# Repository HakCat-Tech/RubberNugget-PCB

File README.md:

# RubberNugget PCB v1.0 (alpha)
PCB design files for the RubberNugget.  More documentation coming soon!

## Features
- ESP32-S2 WiFi MicroController
- Native USB
- JTAG Debug
- Expansion Headers
- UART Breakout
- Qwiic Connector
- NeoPixel Breakout

## Fixes
- [ ] Antenna clearance
- [ ] Component layout
- [ ] Header pinout standard
- [ ] PCB Art

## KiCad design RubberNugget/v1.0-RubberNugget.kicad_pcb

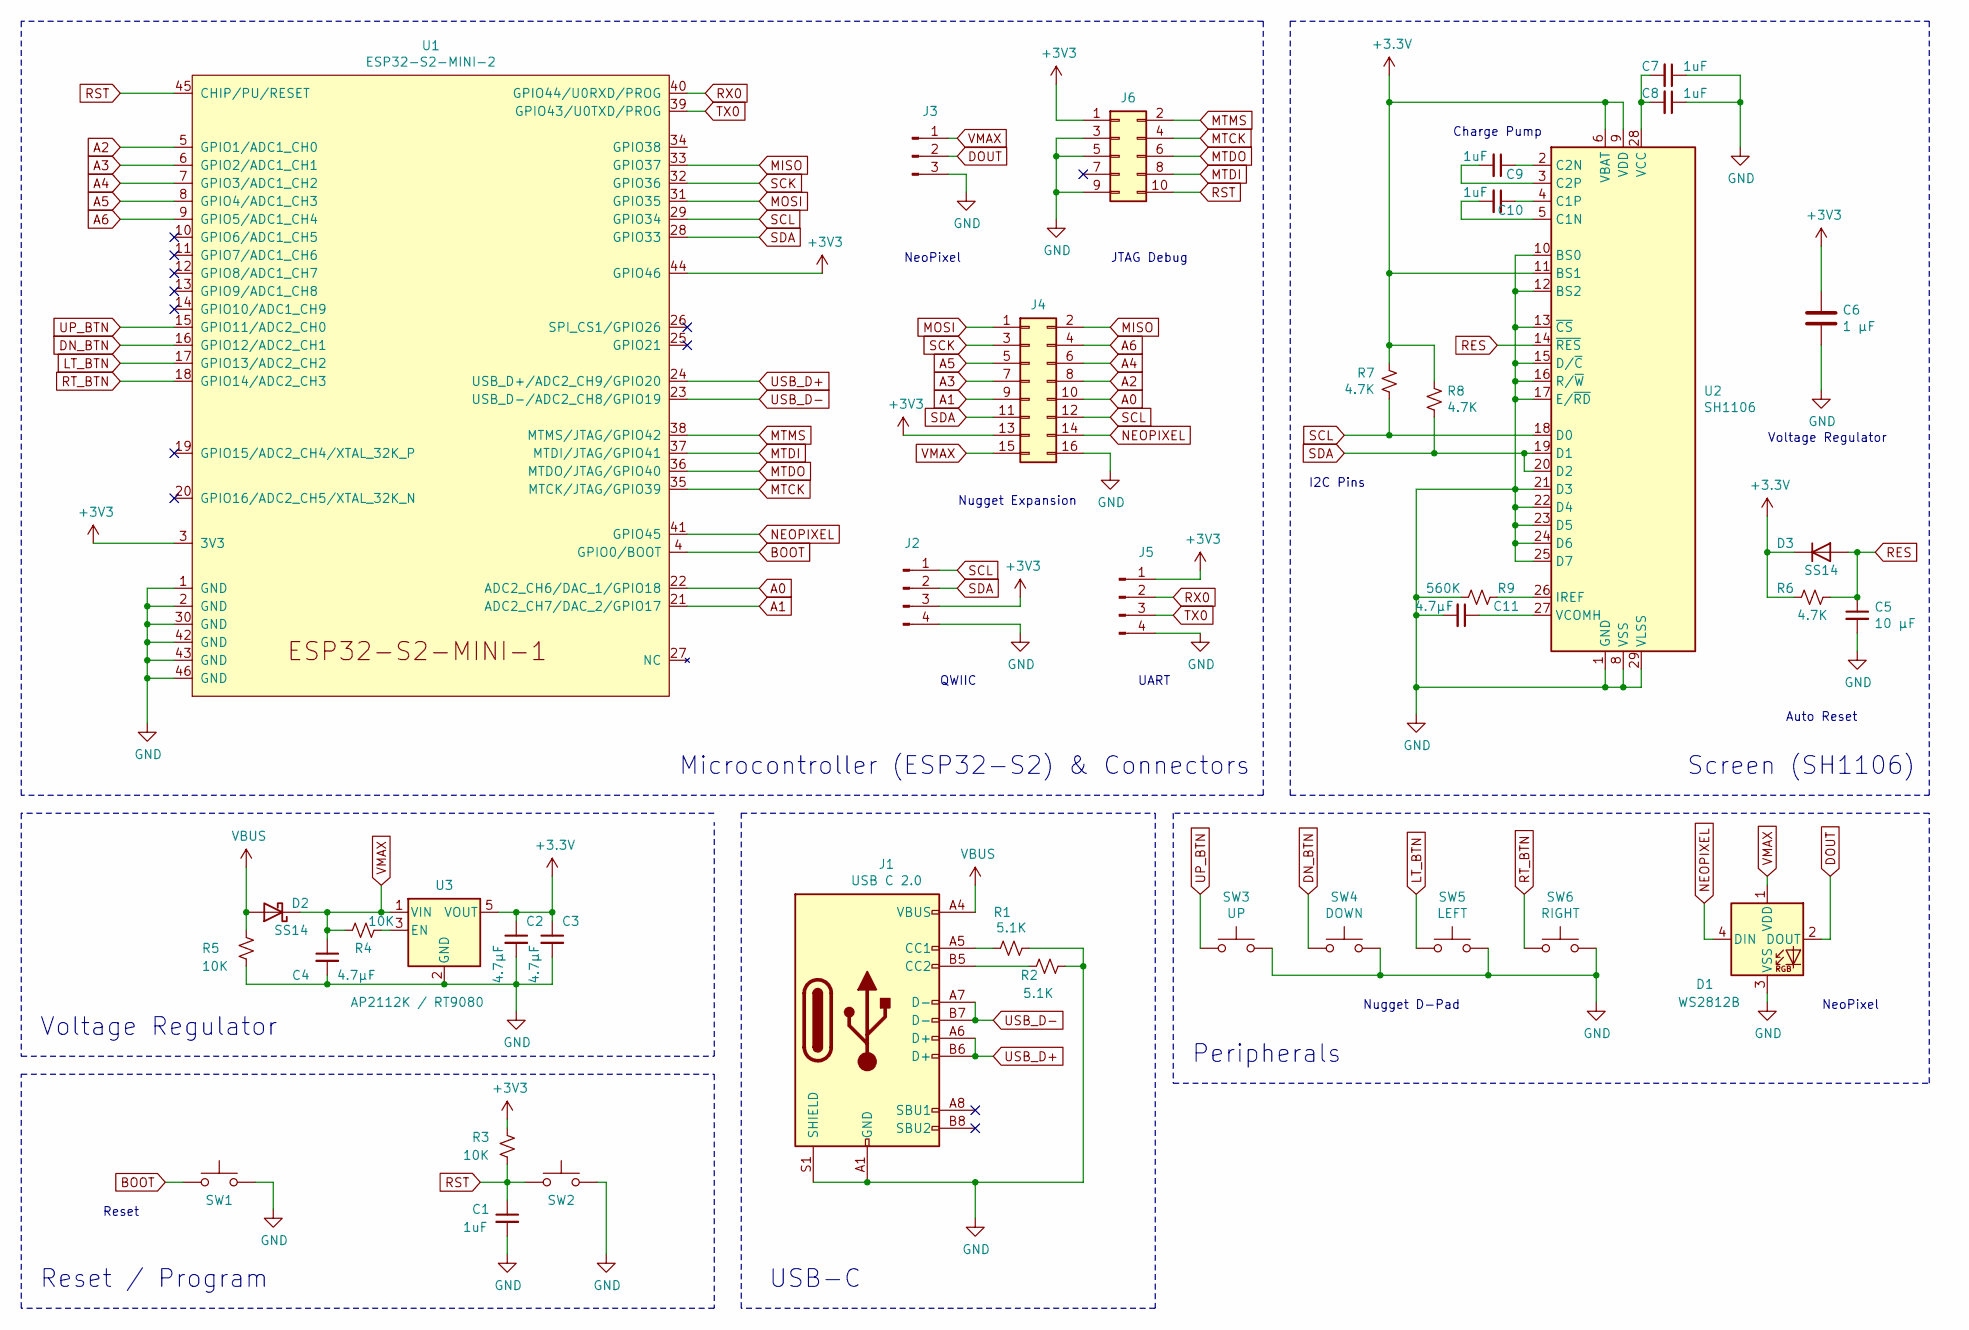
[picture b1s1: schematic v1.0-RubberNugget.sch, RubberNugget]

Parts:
C1, C7, C8, C9, C10: 1uF; C_0603_1608Metric_Pad1.08x0.95mm_HandSolder
C2, C3, C4, C11: 4.7μF; C_0603_1608Metric_Pad1.08x0.95mm_HandSolder
C5: 10 μF; C_0603_1608Metric_Pad1.08x0.95mm_HandSolder
C6: 1 μF; C_0603_1608Metric_Pad1.08x0.95mm_HandSolder
D1: WS2812B; LED_WS2812B_PLCC4_5.0x5.0mm_P3.2mm
D2, D3: SS14; D_SOD-323_HandSoldering
J1: USB C 2.0; USB_C_Receptacle_Palconn_UTC16-G
J2: QWIIC; JST_SH_SM04B-SRSS-TB_1x04-1MP_P1.00mm_Horizontal
J3: NeoPixel Breakout; JST_SH_SM03B-SRSS-TB_1x03-1MP_P1.00mm_Horizontal
J4: Nugget Expansion; PinHeader_2x08_P1.27mm_Vertical_SMD
J5: UART; JST_SH_SM04B-SRSS-TB_1x04-1MP_P1.00mm_Horizontal
J6: JTAG; PinHeader_2x05_P1.27mm_Vertical_SMD
R1, R2: 5.1K; R_0603_1608Metric_Pad0.98x0.95mm_HandSolder
R3, R4, R5: 10K; R_0603_1608Metric_Pad0.98x0.95mm_HandSolder
R6, R7, R8: 4.7K; R_0603_1608Metric_Pad0.98x0.95mm_HandSolder
R9: 560K; R_0603_1608Metric_Pad0.98x0.95mm_HandSolder
SW1, SW2: Reset; Panasonic_EVQPUM_EVQPUD
SW3: UP; SW_SPST_FSMSM
SW4: DOWN; SW_SPST_FSMSM
SW5: LEFT; SW_SPST_FSMSM
SW6: RIGHT; SW_SPST_FSMSM
U1: ESP32-S2-MINI-2; ESP32-S2-MINI-1_Hand-Soldering
U2: SH1106; OLED-128O064D
U3: AP2112K / RT9080; SOT-23-5

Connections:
A0: J4.10, U1.22 (ADC2_CH6/DAC_1/GPIO18)
A1: J4.9, U1.21 (ADC2_CH7/DAC_2/GPIO17)
A2: J4.8, U1.5 (GPIO1/ADC1_CH0)
A3: J4.7, U1.6 (GPIO2/ADC1_CH1)
A4: J4.6, U1.7 (GPIO3/ADC1_CH2)
A5: J4.5, U1.8 (GPIO4/ADC1_CH3)
A6: J4.4, U1.9 (GPIO5/ADC1_CH4)
BOOT: SW1.1, U1.4 (GPIO0/BOOT)
DN_BTN: SW4.1, U1.16 (GPIO12/ADC2_CH1)
DOUT: D1.2 (DOUT), J3.2
GND: C1.2, C2.2, C3.2, C4.2, C5.2, C6.2, C7.1, C8.1, C11.2, D1.3 (VSS), J1.A1 (GND), J1.A12 (GND), J1.B1 (GND), J1.B12 (GND), J1.S1 (SHIELD), J2.4, J3.3, J4.16, J5.4, J6.3, J6.5, J6.9, R1.1, R2.2, R5.2, R9.2, SW1.2, SW2.2, SW3.2, SW4.2, SW5.2, SW6.2, U1.1 (GND), U1.2 (GND), U1.30 (GND), U1.42 (GND), U1.43 (GND), U1.46 (GND), U2.1 (GND), U2.8 (VSS), U2.10 (BS0), U2.12 (BS2), U2.13 (~CS), U2.15 (D/~C), U2.16 (R/~W), U2.17 (E/~RD), U2.21 (D3), U2.22 (D4), U2.23 (D5), U2.24 (D6), U2.25 (D7), U2.29 (VLSS), U2.30 (GND), U3.2 (GND)
LT_BTN: SW5.1, U1.17 (GPIO13/ADC2_CH2)
MISO: J4.2, U1.33 (GPIO37)
MOSI: J4.1, U1.31 (GPIO35)
MTCK: J6.4, U1.35 (MTCK/JTAG/GPIO39)
MTDI: J6.8, U1.37 (MTDI/JTAG/GPIO41)
MTDO: J6.6, U1.36 (MTDO/JTAG/GPIO40)
MTMS: J6.2, U1.38 (MTMS/JTAG/GPIO42)
NEOPIXEL: D1.4 (DIN), J4.14, U1.41 (GPIO45)
unnamed: C7.2, C8.2, U2.28 (VCC)
unnamed: C9.1, U2.2 (C2N)
unnamed: C9.2, U2.3 (C2P)
unnamed: C10.1, U2.4 (C1P)
unnamed: C10.2, U2.5 (C1N)
unnamed: C11.1, U2.27 (VCOMH)
unnamed: J1.A5 (CC1), R1.2
unnamed: J1.B5 (CC2), R2.1
unnamed: R4.1, U3.3 (EN)
unnamed: R9.1, U2.26 (IREF)
RES: C5.1, D3.2 (A), R6.1, U2.14 (~RES)
RST: C1.1, J6.10, R3.2, SW2.1, U1.45 (CHIP/PU/RESET)
RT_BTN: SW6.1, U1.18 (GPIO14/ADC2_CH3)
RX0: J5.2, U1.40 (GPIO44/U0RXD/PROG)
SCK: J4.3, U1.32 (GPIO36)
SCL: J2.1, J4.12, R7.2, U1.29 (GPIO34), U2.18 (D0)
SDA: J2.2, J4.11, R8.2, U1.28 (GPIO33), U2.19 (D1), U2.20 (D2)
TX0: J5.3, U1.39 (GPIO43/U0TXD/PROG)
UP_BTN: SW3.1, U1.15 (GPIO11/ADC2_CH0)
USB_D+: J1.A6 (D+), J1.B6 (D+), U1.24 (USB_D+/ADC2_CH9/GPIO20)
USB_D-: J1.A7 (D-), J1.B7 (D-), U1.23 (USB_D-/ADC2_CH8/GPIO19)
VBUS: D2.2 (A), J1.A4 (VBUS), J1.A9 (VBUS), J1.B4 (VBUS), J1.B9 (VBUS), R5.1
VMAX: C4.1, D1.1 (VDD), D2.1 (K), J3.1, J4.15, R4.2, U3.1 (VIN)

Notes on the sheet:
Microcontroller (ESP32-S2) & Connectors
Voltage Regulator
Auto Reset
I2C Pins
Charge Pump
NeoPixel
Nugget D-Pad
Screen (SH1106)
Peripherals
USB-C
Reset
Voltage Regulator
Reset / Program
QWIIC
NeoPixel
UART
JTAG Debug
Nugget Expansion

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
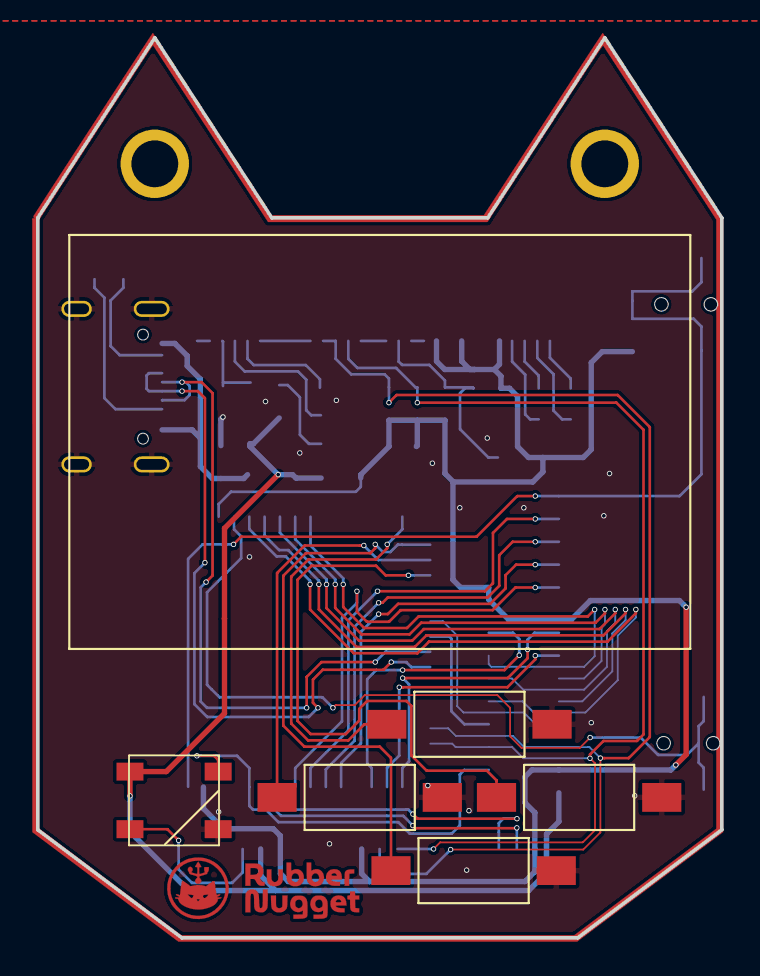
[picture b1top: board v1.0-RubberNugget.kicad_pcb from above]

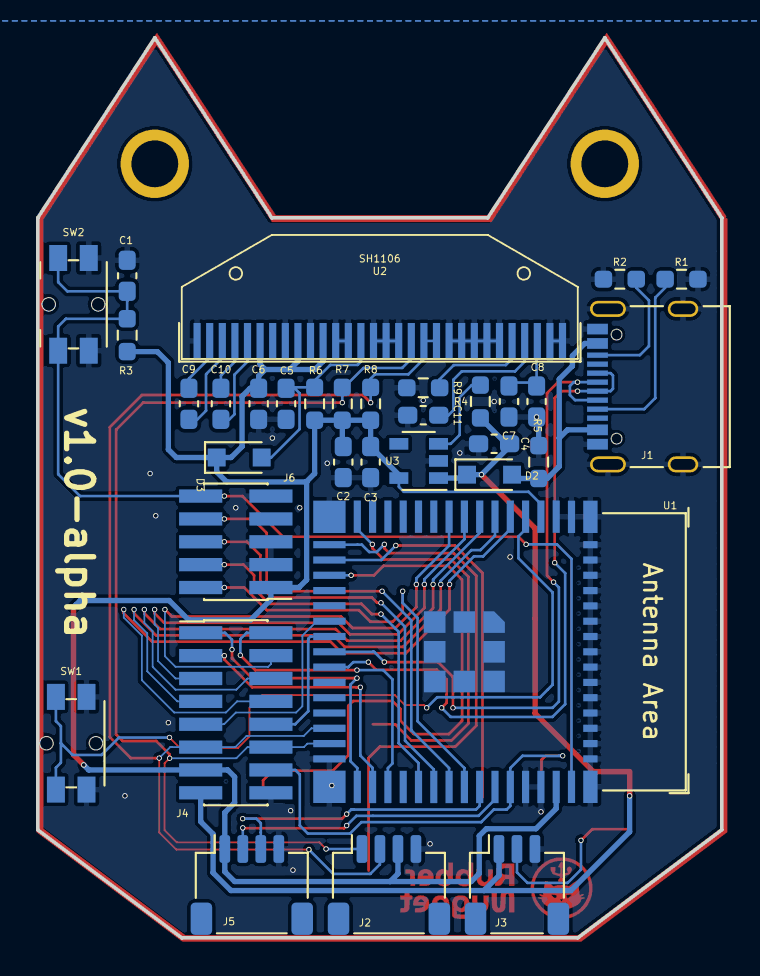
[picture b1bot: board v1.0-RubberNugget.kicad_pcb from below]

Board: 2 copper layers, 38.0 x 50.0 mm, 39 parts (33 on the bottom side), 43 nets.

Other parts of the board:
Ref**: Val**; art

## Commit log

2022-05-02 v1.0 RubberNugget schematic
2022-05-02 fix submodule
2022-05-21 update and re-wire v1.0 alpha
